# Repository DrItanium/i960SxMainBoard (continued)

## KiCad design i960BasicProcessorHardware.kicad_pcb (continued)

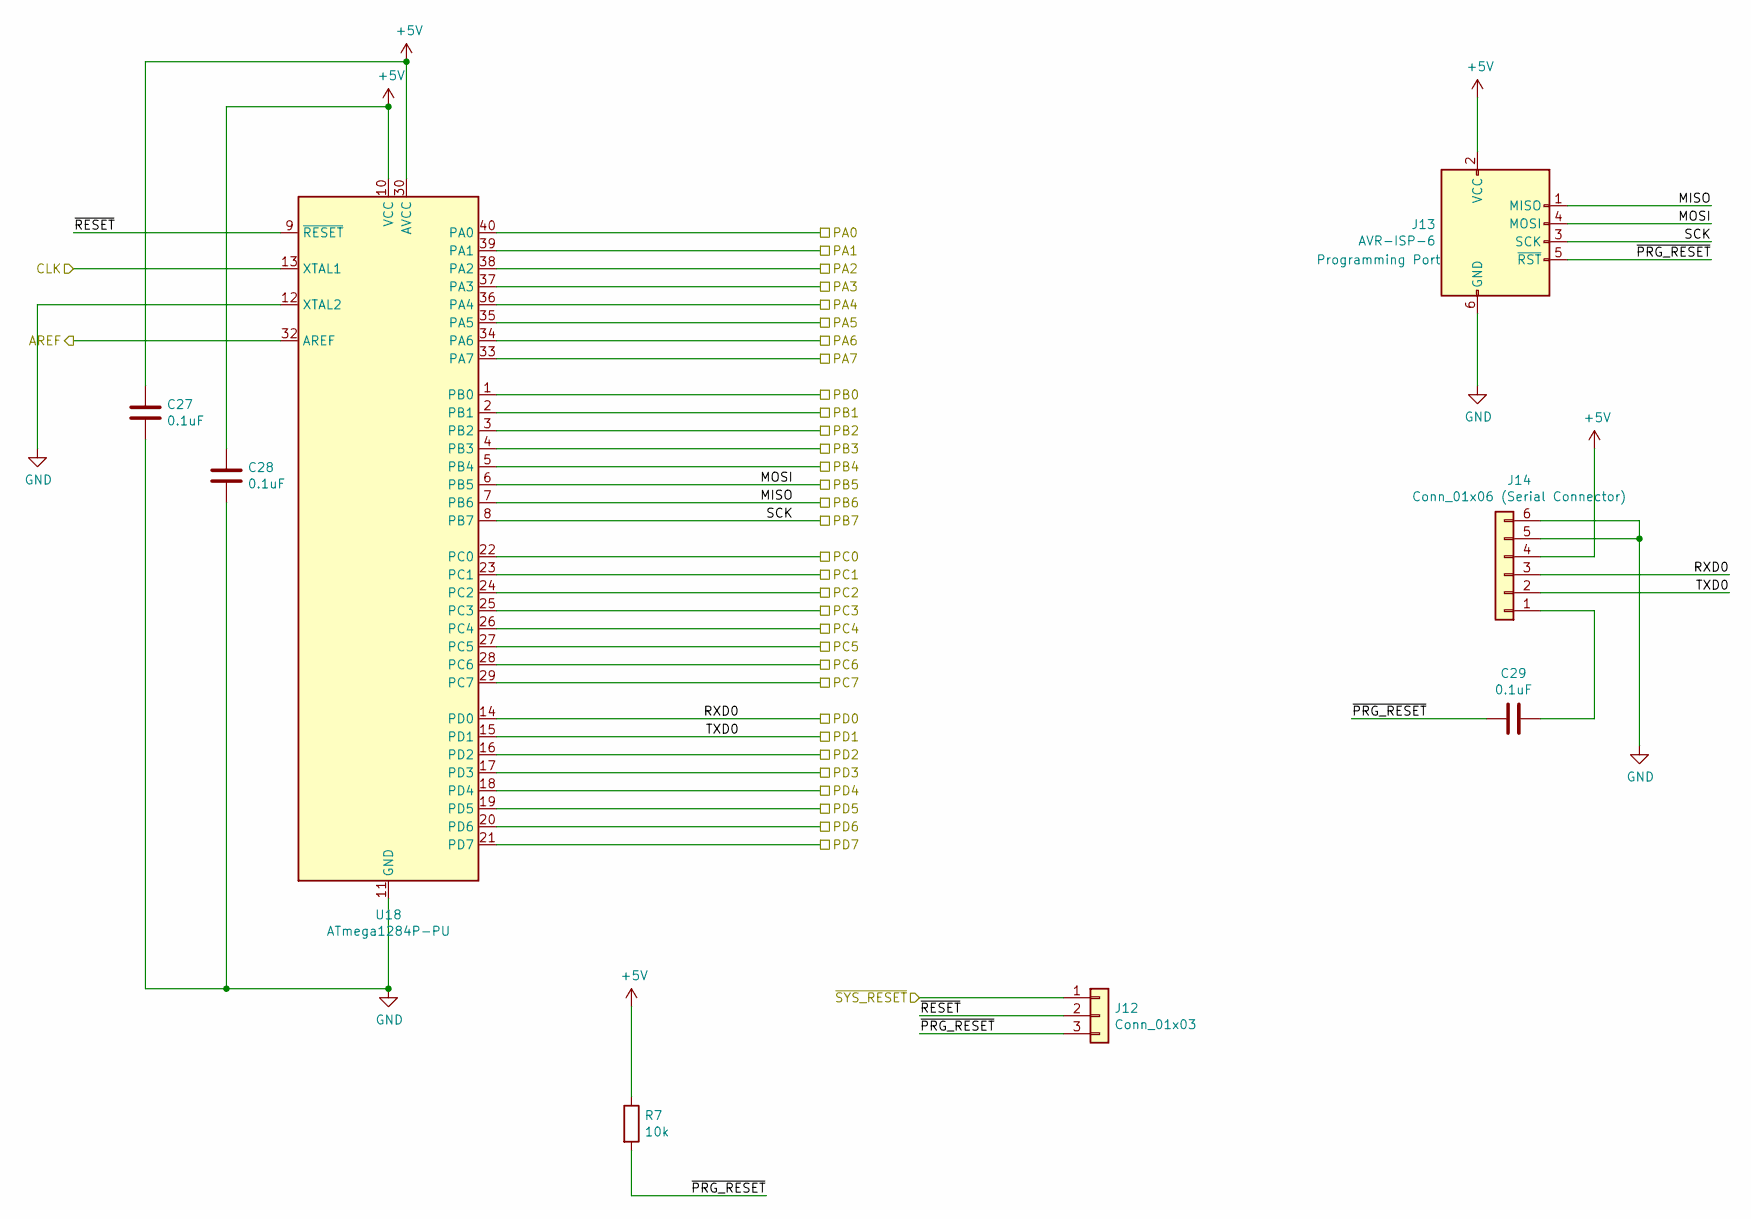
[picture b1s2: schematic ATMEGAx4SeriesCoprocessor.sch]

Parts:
C27, C28, C29: 0.1uF; C_0805_2012Metric_Pad1.18x1.45mm_HandSolder
J12: Conn_01x03; PinHeader_1x03_P2.54mm_Vertical
J13: AVR-ISP-6; PinHeader_2x03_P2.54mm_Vertical
J14: Conn_01x06 (Serial Connector); PinHeader_1x06_P2.54mm_Vertical
R7: 10k; R_0805_2012Metric_Pad1.20x1.40mm_HandSolder
U18: ATmega1284P-PU; DIP-40_W15.24mm_Socket

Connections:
+5V: C27.1, C28.1, J13.2 (VCC), J14.4, R7.1, U18.10 (VCC), U18.30 (AVCC); also elsewhere on the board
/COPROC0_AREF: U18.32 (AREF); also elsewhere on the board
/COPROC0_PA0: U18.40 (PA0); also elsewhere on the board
/COPROC0_PA1: U18.39 (PA1); also elsewhere on the board
/COPROC0_PA2: U18.38 (PA2); also elsewhere on the board
/COPROC0_PA3: U18.37 (PA3); also elsewhere on the board
/COPROC0_PA4: U18.36 (PA4); also elsewhere on the board
/COPROC0_PA5: U18.35 (PA5); also elsewhere on the board
/COPROC0_PA6: U18.34 (PA6); also elsewhere on the board
/COPROC0_PA7: U18.33 (PA7); also elsewhere on the board
/COPROC0_PB0: U18.1 (PB0); also elsewhere on the board
/COPROC0_PB1: U18.2 (PB1); also elsewhere on the board
/COPROC0_PB2: U18.3 (PB2); also elsewhere on the board
/COPROC0_PB3: U18.4 (PB3); also elsewhere on the board
/COPROC0_PB4: U18.5 (PB4); also elsewhere on the board
/COPROC0_PB5: J13.4 (MOSI), U18.6 (PB5); also elsewhere on the board
/COPROC0_PB6: J13.1 (MISO), U18.7 (PB6); also elsewhere on the board
/COPROC0_PB7: J13.3 (SCK), U18.8 (PB7); also elsewhere on the board
/COPROC0_PC0: U18.22 (PC0); also elsewhere on the board
/COPROC0_PC1: U18.23 (PC1); also elsewhere on the board
/COPROC0_PC2: U18.24 (PC2); also elsewhere on the board
/COPROC0_PC3: U18.25 (PC3); also elsewhere on the board
/COPROC0_PC4: U18.26 (PC4); also elsewhere on the board
/COPROC0_PC5: U18.27 (PC5); also elsewhere on the board
/COPROC0_PC6: U18.28 (PC6); also elsewhere on the board
/COPROC0_PC7: U18.29 (PC7); also elsewhere on the board
/COPROC0_PD0: J14.3, U18.14 (PD0); also elsewhere on the board
/COPROC0_PD1: J14.2, U18.15 (PD1); also elsewhere on the board
/COPROC0_PD2: U18.16 (PD2); also elsewhere on the board
/COPROC0_PD3: U18.17 (PD3); also elsewhere on the board
/COPROC0_PD4: U18.18 (PD4); also elsewhere on the board
/COPROC0_PD5: U18.19 (PD5); also elsewhere on the board
/COPROC0_PD6: U18.20 (PD6); also elsewhere on the board
/COPROC0_PD7: U18.21 (PD7); also elsewhere on the board
/EXTCLK: U18.13 (XTAL1); also elsewhere on the board
/Sheet7D8CCC79/~PRG_RESET: C29.2, J12.3, J13.5 (~RST), R7.2
/Sheet7D8CCC79/~RESET: J12.2, U18.9 (~RESET)
/~MCU_RESET: J12.1; also elsewhere on the board
GND: C27.2, C28.2, J13.6 (GND), J14.5, J14.6, U18.11 (GND), U18.12 (XTAL2), U18.31 (GND); also elsewhere on the board
unnamed: C29.1, J14.1

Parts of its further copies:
C30, C31, C32: 0.1uF; C_0805_2012Metric_Pad1.18x1.45mm_HandSolder
J22: Conn_01x03; PinHeader_1x03_P2.54mm_Vertical
J23: AVR-ISP-6; PinHeader_2x03_P2.54mm_Vertical
J24: Conn_01x06 (Serial Connector); PinHeader_1x06_P2.54mm_Vertical
R8: 10k; R_0805_2012Metric_Pad1.20x1.40mm_HandSolder
U19: ATmega1284P-PU; DIP-40_W15.24mm_Socket

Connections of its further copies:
+5V: C30.1, C31.1, J23.2 (VCC), J24.4, R8.1, U19.10 (VCC), U19.30 (AVCC); also elsewhere on the board
/COPROC1_AREF: U19.32 (AREF); also elsewhere on the board
/COPROC1_PA0: U19.40 (PA0); also elsewhere on the board
/COPROC1_PA1: U19.39 (PA1); also elsewhere on the board
/COPROC1_PA2: U19.38 (PA2); also elsewhere on the board
/COPROC1_PA3: U19.37 (PA3); also elsewhere on the board
/COPROC1_PA4: U19.36 (PA4); also elsewhere on the board
/COPROC1_PA5: U19.35 (PA5); also elsewhere on the board
/COPROC1_PA6: U19.34 (PA6); also elsewhere on the board
/COPROC1_PA7: U19.33 (PA7); also elsewhere on the board
/COPROC1_PB0: U19.1 (PB0); also elsewhere on the board
/COPROC1_PB1: U19.2 (PB1); also elsewhere on the board
/COPROC1_PB2: U19.3 (PB2); also elsewhere on the board
/COPROC1_PB3: U19.4 (PB3); also elsewhere on the board
/COPROC1_PB4: U19.5 (PB4); also elsewhere on the board
/COPROC1_PB5: J23.4 (MOSI), U19.6 (PB5); also elsewhere on the board
/COPROC1_PB6: J23.1 (MISO), U19.7 (PB6); also elsewhere on the board
/COPROC1_PB7: J23.3 (SCK), U19.8 (PB7); also elsewhere on the board
/COPROC1_PC0: U19.22 (PC0); also elsewhere on the board
/COPROC1_PC1: U19.23 (PC1); also elsewhere on the board
/COPROC1_PC2: U19.24 (PC2); also elsewhere on the board
/COPROC1_PC3: U19.25 (PC3); also elsewhere on the board
/COPROC1_PC4: U19.26 (PC4); also elsewhere on the board
/COPROC1_PC5: U19.27 (PC5); also elsewhere on the board
/COPROC1_PC6: U19.28 (PC6); also elsewhere on the board
/COPROC1_PC7: U19.29 (PC7); also elsewhere on the board
/COPROC1_PD0: J24.3, U19.14 (PD0); also elsewhere on the board
/COPROC1_PD1: J24.2, U19.15 (PD1); also elsewhere on the board
/COPROC1_PD2: U19.16 (PD2); also elsewhere on the board
/COPROC1_PD3: U19.17 (PD3); also elsewhere on the board
/COPROC1_PD4: U19.18 (PD4); also elsewhere on the board
/COPROC1_PD5: U19.19 (PD5); also elsewhere on the board
/COPROC1_PD6: U19.20 (PD6); also elsewhere on the board
/COPROC1_PD7: U19.21 (PD7); also elsewhere on the board
/EXTCLK: U19.13 (XTAL1); also elsewhere on the board
/sheet847B5775/~PRG_RESET: C32.2, J22.3, J23.5 (~RST), R8.2
/sheet847B5775/~RESET: J22.2, U19.9 (~RESET)
/~MCU_RESET: J22.1; also elsewhere on the board
GND: C30.2, C31.2, J23.6 (GND), J24.5, J24.6, U19.11 (GND), U19.12 (XTAL2), U19.31 (GND); also elsewhere on the board
unnamed: C32.1, J24.1

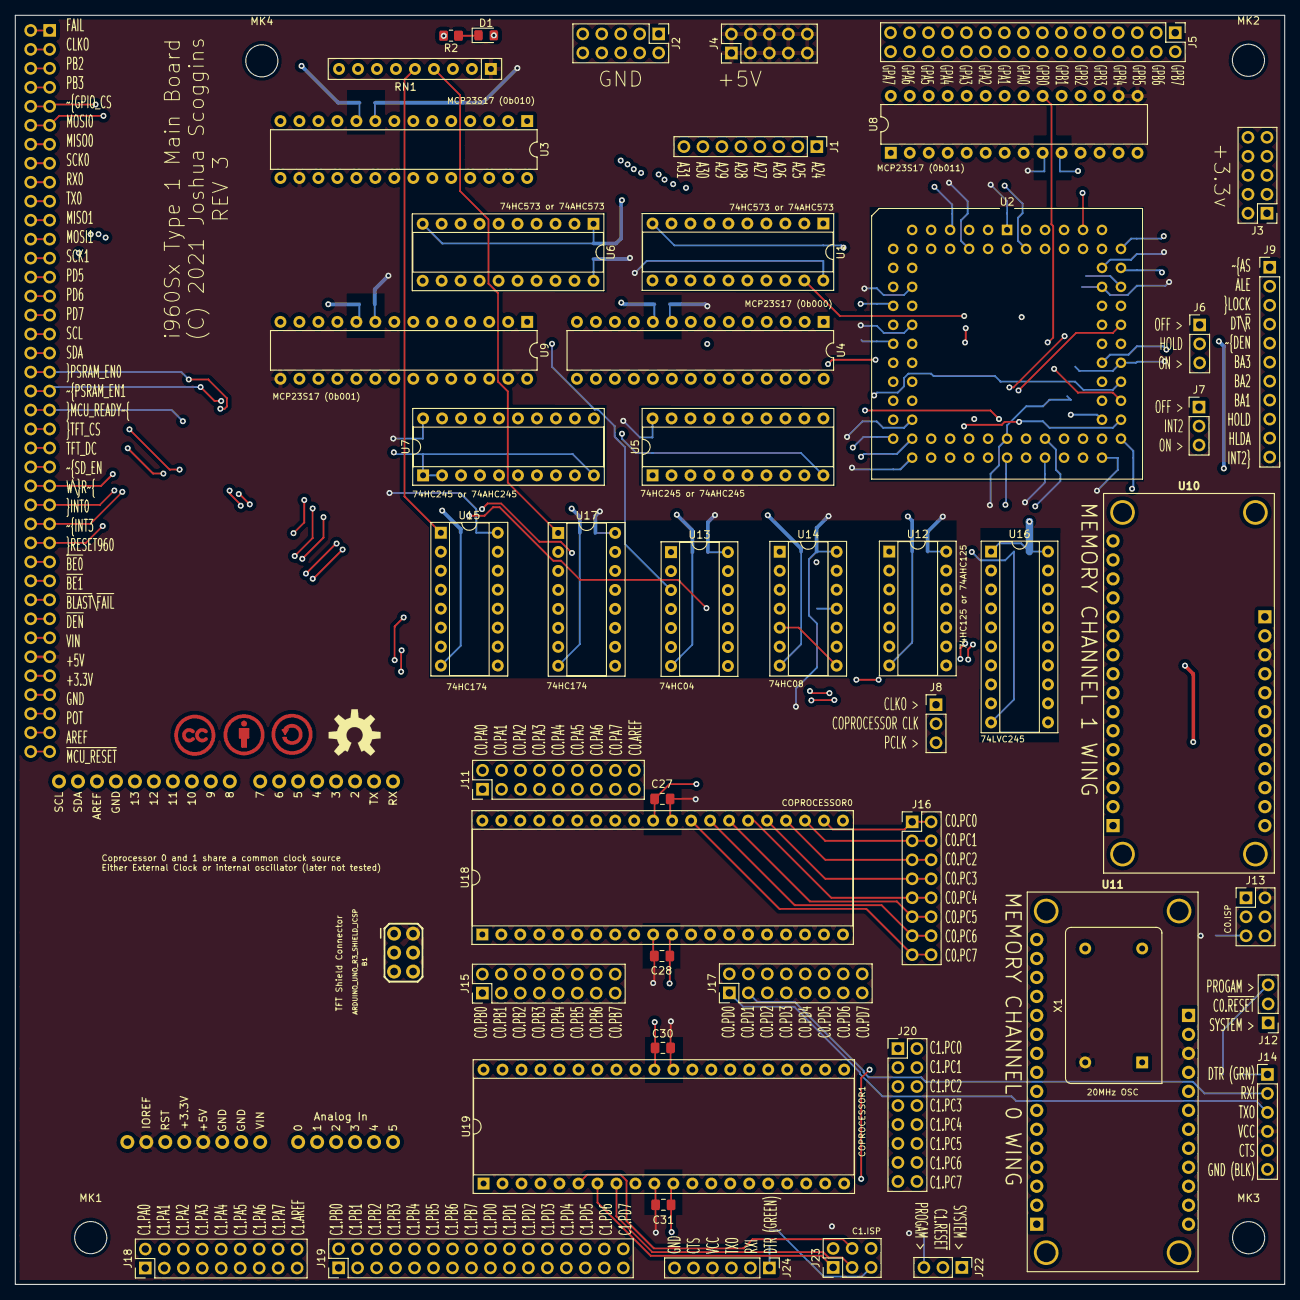
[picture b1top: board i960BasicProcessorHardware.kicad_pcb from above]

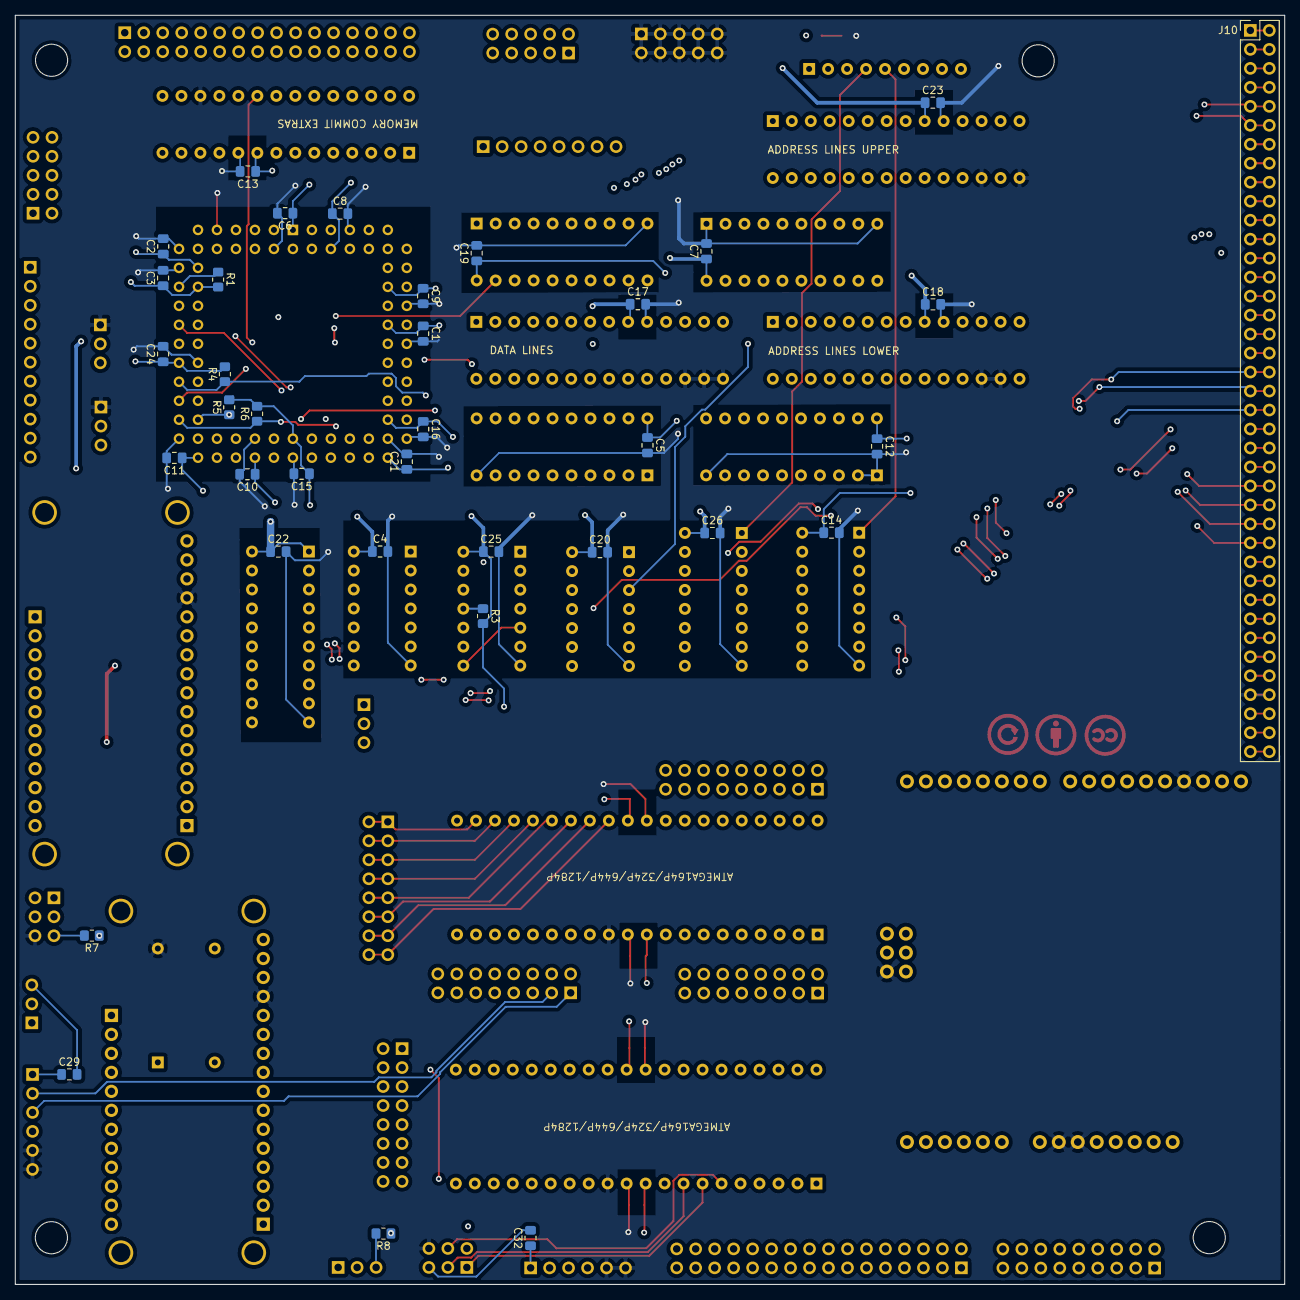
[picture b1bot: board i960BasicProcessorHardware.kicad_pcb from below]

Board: 4 copper layers, 169.9 x 169.8 mm, 90 parts (36 on the bottom side), 229 nets.

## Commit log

2021-10-16 README.md
2021-10-16 Added a license (CC-BY-SA)
    Normally it would be BSD or zlib but in this case CC-BY-SA makes a lot
    more sense for hardware.
2021-10-16 move RESET960 and INT0 to the ioexpander
    PORTA on the fourth ioexpander is now fully populated.
    I am thinking of rearranging the pinout so that the analog pins are not
    in the middle of the analog port.
2021-10-16 Move ~MCU_READY to PC4
    Added a pullup resistor to ~RESET960 to be on the safe side.
    PA1, PA2, and PA3 are now the free pins in PORTA
2021-10-16 Updated pcb to reflect new design changes
2021-10-16 Update revision number
2021-10-16 Finish initial rev2
2021-10-16 move int0 back to the microcontroller and int1 to inta of 0b011 io expander
2021-10-16 Added an attiny85 for programming purposes
    It will be there solely for research purposes. It's clock will not be
    tied in at all, it is there for the purpose of trying stuff out.
    I also moved hold,hlda, and ~LOCK to the breakout header that ~AS, ALE,
    and others are attached to. I have plans to move ~INT3 to the
    microcontroller. I am also planning to expose the reset pin to the
    i960 itself so it can do a software reset.
2021-10-16 part selection and fill removal
2021-10-16 Finished adding the attiny85
2021-10-16 moved int2 and int3 to the signal breakout
    I did not directly connect ~int3 to the microcontroller setup. I want to
    leave it free for any future design ideas. Clock synchronization is
    important but not impossible to work around.
    I am still wondering if I should break the 8 most significant bits of
    the address out to a separate header for future expansion effort.
2021-10-16 Decided to break the highest 8 bits of the address out to a separate header.
    I've done it before when I made the processor card interface. I can
    position it fairly close without fear of signal degredation
2021-10-16 Rearrange some of the board and move the interrupt pull ups to individual resistors
2021-10-16 Upper 8 breakout successfully routed in
2021-10-16 Separate ~RESET960's pullup to a separate resistor
    I have plenty of space underneath the plcc socket for resistors
2021-10-16 move ~RESET960 back to the primary chipset
    also move ~INT3 to it as well. I want two different interrupt pins
    accessible to the primary chipset. I have made the fourth ioexpander
    completely exposed to the i960.
2021-10-16 Wireup the fourth gpio expander
2021-10-16 Update labels and delete bad trace
2021-10-16 Drop the attiny85 because I'm going to put several extra attiny861s in its place
2021-10-16 Drop the attiny85
    I am going to place two 861s instead tied to the same 20mhz clock
    I am also considering adding a dip40 socket also tied to the same
    20mhz clock
2021-10-16 Move the attiny861 schematic to a sub schematic
    I am planning to have multiple of them
2021-10-16 Breakout other lines
2021-10-16 fixup int0 for the attiny861 to be pb6
    Add a second attiny861
2021-10-16 We always have access to the 861s
2021-10-16 pull in a 1284p socket setup
2021-10-16 Drop the attiny861s and add the 1284p based coprocessor in its place
2021-10-16 ATMEGAx4 coprocessor is basically setup
2021-10-16 Partially pinout the extra x4 hardware
2021-10-16 start moving the 74lvc245 to free up some space
2021-10-16 Add an onboard oscillator when it is necessary to program the secondary processor
2021-10-16 Drop the extra breakout for spi
2021-10-16 Move the coprocessor clock source selector to the main page
2021-10-17 breakout all of the coprocessor0 pins to separate headers
    Bundle the AREF pin with PORTA
2021-10-17 Double headers for each co processor
    Added a second coprocessor
2021-10-17 Keep futzing with the design
    Added a missing +5v power source to the x4 coprocessor schematic
2021-10-17 Rudimentary layout
2021-10-17 Get the two co processors laid out properly and start wiring it up
2021-10-17 Finish cleaning up rev3 for now the layout is complete
2021-10-17 First version of rev3 done
2021-10-17 Finished labeling everything
2021-10-17 Fix placement of info tag
2021-10-17 Added a pullup resistor for each programming reset line
2021-10-17 Installed the two missing pullup resistors
2021-10-17 Text modifications and license additions
2021-10-17 Fix names
2021-10-17 Get more space
2021-10-20 Added rev3 images
